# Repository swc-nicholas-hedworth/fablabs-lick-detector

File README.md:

# Fablabs Lick Detector

Inspired by the Allen Institute's: https://github.com/AllenNeuralDynamics/harp.device.lickety-split

## 1. Introduction

Capacitive lick detection offer advantages in the accuracy and speed of lick/touch detection. The challenge comes when using it with ephys devices such as the neuropixel which can pickup the input signal from the touch detector as noise. Our lick detector was inspired by the Allen Institutes lick detector which is shown to have low impact on ephys recordings.

The goals for this device were as follows:
- Reliable lick detection
- Low noise on ephys readings
- Simple to adjust and debug
- Easy to manufacture
- Easy to adapt into your own design

## 2. Setup
### Power Supply Requirements
- Min. Voltage = 3V
- Max. Voltage = 5.5V
- Max Current Consumption = 70mA (regardless of input voltage).

The output TTL depends on the input VCC voltage. For example:
- If VCC = 3.3V, output TTL amplitude = 3.3V
- If VCC = 5V, output TTL amplitude = 5V

### Ground Connection
Although not strictly necessary, it is encouraged for the mouse to have a reference to the board's ground potential. Basically the mouse needs to touch a conductor which is connected to the board's 

#### Metalic Floor
if the floor the mouse stands on is conductive, you may connect this floor to the ground potential.

#### Ephys
If the mouse has an implanted ephys device, it is posssible to connect the board's ground to that of the implant's ground.

### Spout Connection
Using crocodile clip

## 3. Calibration

This section outlines how to set the positions of the potentiometers RV1 and RV2 without any specialised equipment.

If any steps do not work, see the debugging guide.

### Step 0: Theory
RV1 is used to set the oscillators gain. clockwise increases the gain. The goal is to have the gain as low as possible to produce a low amplitude and clean signal to the spout so as to not intefere with ephys measurements. At maximum gain the signal will be distorted, introducing harmonics to the signal which is undesireable. At a certain "minimum" gain the oscillator will stop working. The goal is to have the oscillator just turn on, this gives us the lowest circuit noise.

RV2 is used to set the output gain. clockwise increases the gain. The goal is to have gain as low as possible to achieve extremely fast response to lick events. The output signal goes through a schmitt trigger, ensuring the gain sets the output at just the point the schmitt trigger activates ensures the quickest response times.

### Step 1: Initial conditions
- Turn RV1 all the way clockwise. (max oscillator gain)
- Turn RV2 all the way anticlockwise (min output gain)

This condition ensures that the oscillator is working (although distorted) and that the LED is on.

### Step 2: Detection
- Turn RV2 clockwise until the LED turns off.

You should see the LED turn on when you touch the "SPOUT" pin, and turn back off when you stop touching

### Step 3: Refine
**The following steps reduce the amplitude of the oscillator, thereby giving lower noise to ephys measurements.**

- Turn RV1 anticlockwise until the LED turns on.
- Turn RV2 clockwise until the LED turns back off.
- Test that touching the "SPOUT" pin still turns the LED on.

### Step 4: Repeat

- Repeat Step 3 until the LED seizes to turn off or if the LED starts behaving weirdly.
- When you reach the point that the LED starts behaving weirdly, revert RV1 and RV2 back to the previous state when the LED was still operating successfully.

## 4. Test Results

This section is intended to show the typical performance of the lick detector at each test point, showing how individual parts of the circuit should perform under normal conditions.

A Keysight DSOX1204A was used to capture the waveform and calculate the FFT. A custom BNC to pin header cable was created to feed signals from the board to the oscilloscope.

### [VCC] Input Voltage
The input voltage is used to power the dual supply converter on the board and the output stage op-amp (see amp and TTL test points).

### [V+] Positive Voltage Rail
This supply rail is generated by the dual supply converter.

### [V-] Negative Voltage Rail
This supply rail is generated by the dual supply converter.

### [osc] Oscillator

### [out] Signal to Spout

### [buf] Buffered Signal from Spout

### [hwr] Half Wave Rectifier

### [pfwr] Precision Full Wave Rectifier

### [lpf] Low-Pass Filter

### [amp] Amplifier 

### [TTL] Final Output TTL

### 5. EMI Performance

This section focuses on how the lick detectors near field noise looks like.

#### E-Field

#### H-Field

### 6. Impact on Ephys Recordings

This section evaluates the impact of noise on Ephys Recordings.

A mouse will lick from a spout. We will collect the following readings:
1. **Control**: 
2. **Grounded to Ephys**:
3. **Grounded to Ephys and Conductive Floor**:

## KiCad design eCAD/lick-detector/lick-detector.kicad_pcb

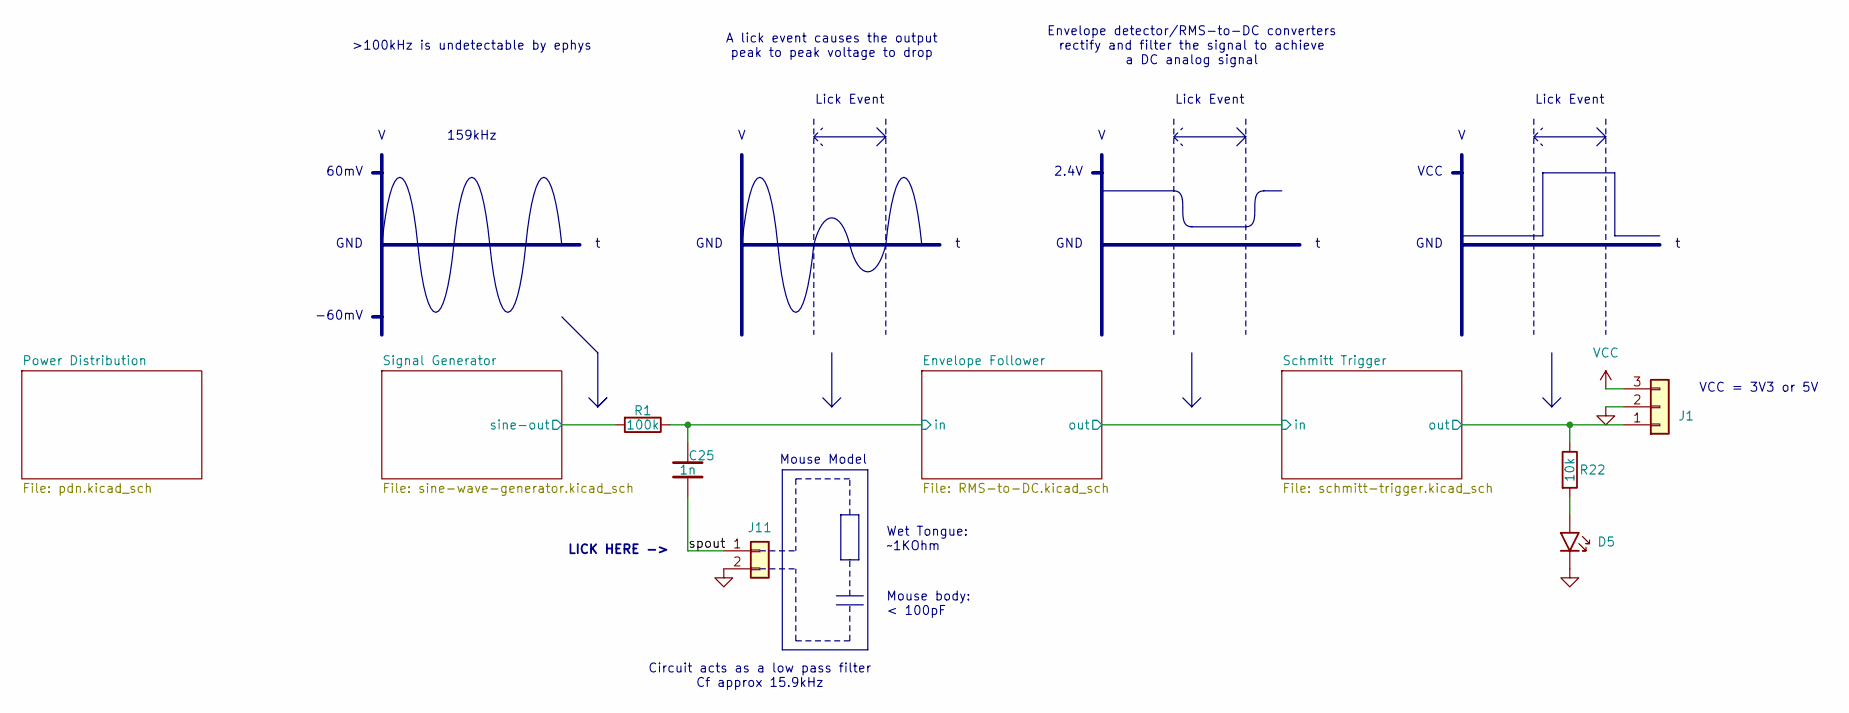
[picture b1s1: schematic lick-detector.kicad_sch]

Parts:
C25: 1n; C_0603_1608M; Part Version 0.0.0; JLCPCB Part # C1588
D5: !LED; LED_0805_2012M; Part Version 0.0.0; JLCPCB Part # C2297
J1: J_PinHeader_01x03_2.54_V; MFR.Part # PZ254V-11-03P; JLCPCB Part # C2937625
J11: J_PinHeader_01x02_2.54_V; MFR.Part # PZ254V-11-02P; JLCPCB Part # C492401
R1: 100k; R_0603_1608M; Part Version 0.0.0; JLCPCB Part # C25803
R22: 10k; R_0603_1608M; Part Version 0.0.0; JLCPCB Part # C25804

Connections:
/RMS-to-DC/in: C25.2, R1.2; also elsewhere on the board
/schmitt-trigger/out: J1.1, R22.2; also elsewhere on the board
/sine-wave-generator/out: R1.1; also elsewhere on the board
/spout: C25.1, J11.1
GND: D5.1 (K), J1.2, J11.2; also elsewhere on the board
unnamed: D5.2 (A), R22.1
VCC: J1.3; also elsewhere on the board

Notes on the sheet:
Lick Event
VCC
A lick event causes the output peak to peak voltage to drop
159kHz
GND
2.4V
>100kHz is undetectable by ephys
Wet Tongue: ~1KOhm
Mouse Model
-60mV
Envelope detector/RMS-to-DC converters rectify and filter the signal to achieve a DC analog signal
LICK HERE ->
VCC = 3V3 or 5V
Mouse body: < 100pF
Circuit acts as a low pass filter Cf approx 15.9kHz
60mV

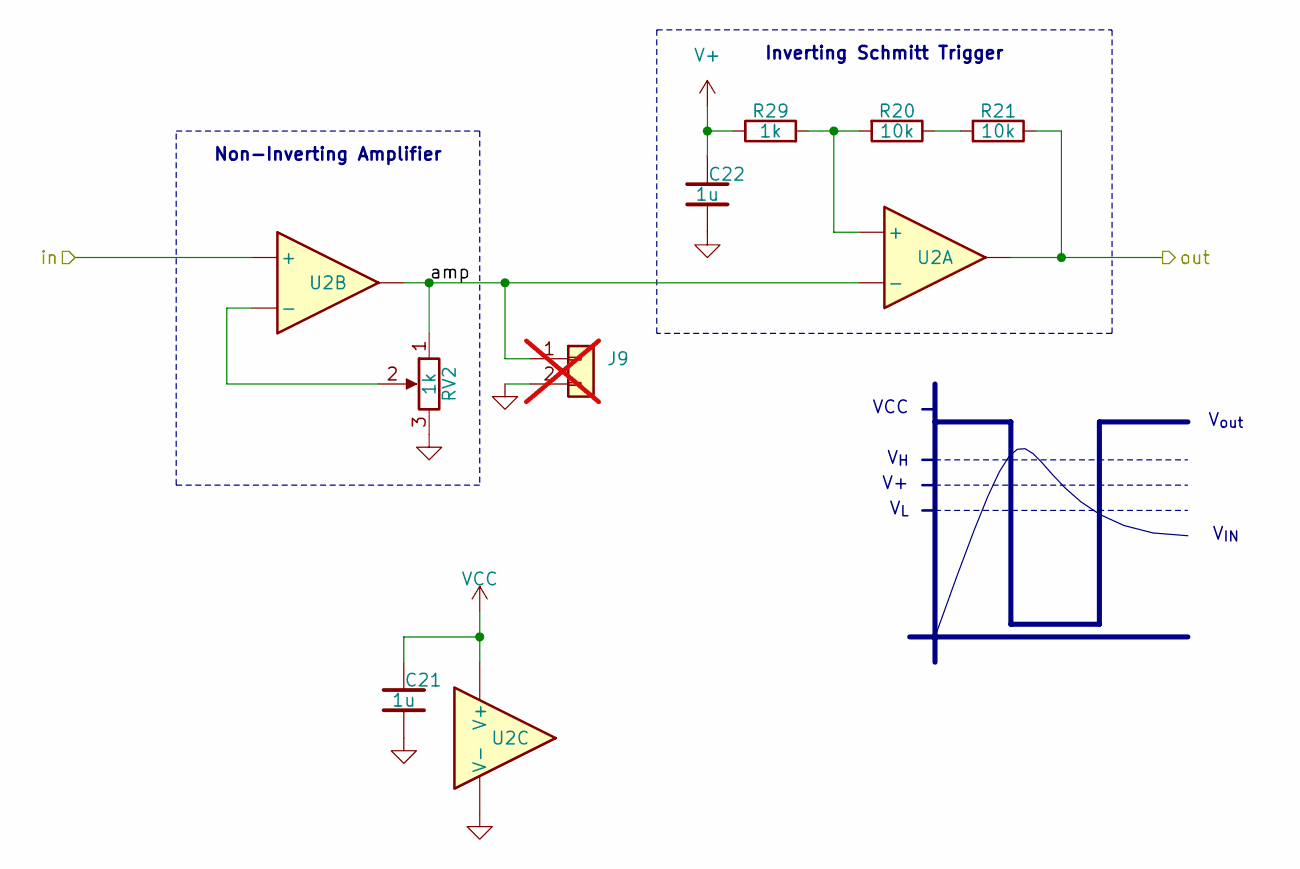
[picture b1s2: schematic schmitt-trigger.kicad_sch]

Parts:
C21, C22: 1u; C_0603_1608M; Part Version 0.0.0; JLCPCB Part # C15849
J9: J_PinHeader_01x02_2.54_V; MFR.Part # PZ254V-11-02P; JLCPCB Part # C492401; not fitted
R20, R21: 10k; R_0603_1608M; Part Version 0.0.0; JLCPCB Part # C25804
R29: 1k; R_0603_1608M; Part Version 0.0.0; JLCPCB Part # C22962
RV2: 1k; 3314J-1-102E; Part Version 0.0.0; JLCPCB Part # C124640
U2: OPA2365; SOIC-8_3.9x4.9mm; Part Version 0.0.0; JLCPCB Part # C130011

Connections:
/RMS-to-DC/lpf: U2.5 (+); also elsewhere on the board
/schmitt-trigger/amp: J9.1, RV2.1, U2.2 (-), U2.7
/schmitt-trigger/out: R21.2, U2.1; also elsewhere on the board
GND: C21.1, C22.1, J9.2, RV2.3, U2.4 (V-); also elsewhere on the board
unnamed: R20.2, R21.1
unnamed: R20.1, R29.1, U2.3 (+)
unnamed: RV2.2, U2.6 (-)
V+: C22.2, R29.2; also elsewhere on the board
VCC: C21.2, U2.8 (V+); also elsewhere on the board

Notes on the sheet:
V_{L}
V_{H}
VCC
V_{out}
V_{IN}
Inverting Schmitt Trigger
Non-Inverting Amplifier

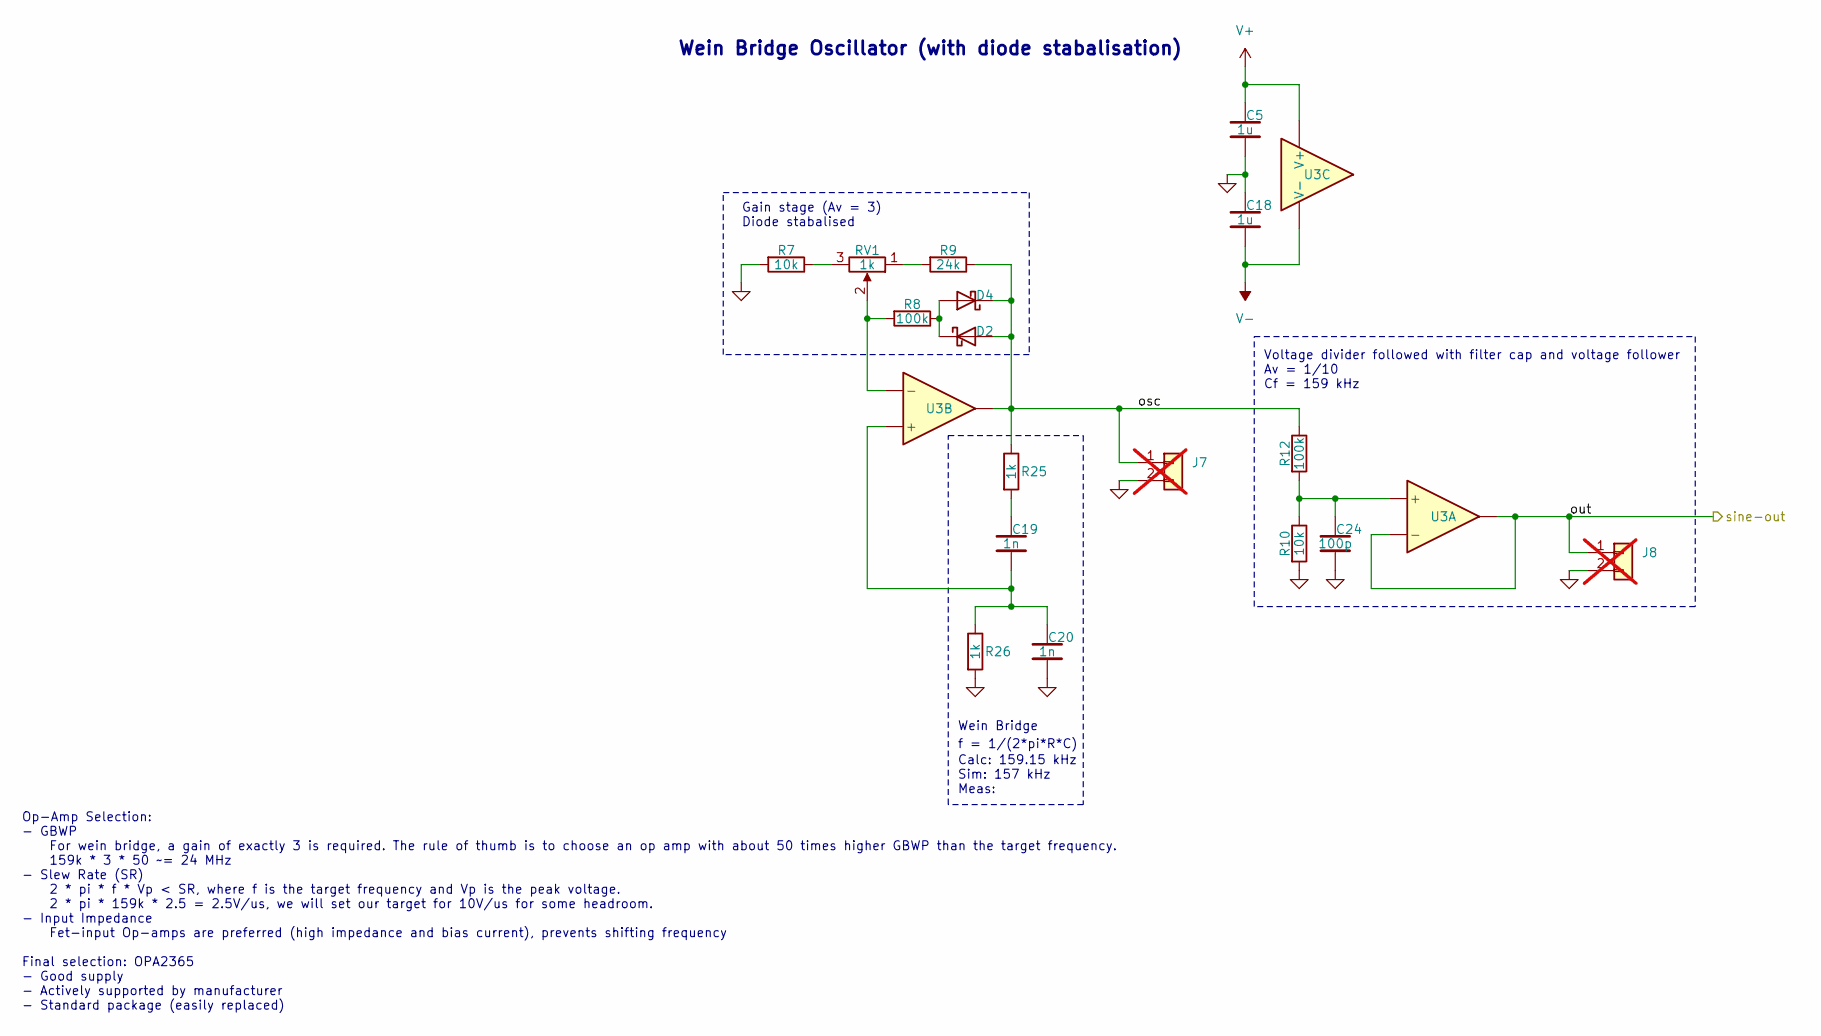
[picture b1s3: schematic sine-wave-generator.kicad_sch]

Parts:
C5, C18: 1u; C_0603_1608M; Part Version 0.0.0; JLCPCB Part # C15849
C19, C20: 1n; C_0603_1608M; Part Version 0.0.0; JLCPCB Part # C1588
C24: 100p; C_0603_1608M; Part Version 0.0.0; JLCPCB Part # C14858
D2, D4: BAT54; SOD-323; Part Version 0.0.0; JLCPCB Part # C21107
J7, J8: J_PinHeader_01x02_2.54_V; MFR.Part # PZ254V-11-02P; JLCPCB Part # C492401; not fitted
R7, R10: 10k; R_0603_1608M; Part Version 0.0.0; JLCPCB Part # C25804
R8, R12: 100k; R_0603_1608M; Part Version 0.0.0; JLCPCB Part # C25803
R9: 24k; R_0603_1608M; Part Version 0.0.0; JLCPCB Part # C23352
R25, R26: 1k; R_0603_1608M; Part Version 0.0.0; JLCPCB Part # C22962
RV1: 1k; 3314J-1-102E; Part Version 0.0.0; JLCPCB Part # C124640
U3: OPA2365; SOIC-8_3.9x4.9mm; Part Version 0.0.0; JLCPCB Part # C130011

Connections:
/sine-wave-generator/osc: D2.2 (A), D4.1 (K), J7.1, R9.2, R12.2, R25.2, U3.7
/sine-wave-generator/out: J8.1, U3.1, U3.2 (-); also elsewhere on the board
GND: C5.1, C18.2, C20.1, C24.1, J7.2, J8.2, R7.1, R10.1, R26.1; also elsewhere on the board
unnamed: C19.2, R25.1
unnamed: D2.1 (K), D4.2 (A), R8.2
unnamed: R7.2, RV1.3
unnamed: R9.1, RV1.1
unnamed: C24.2, R10.2, R12.1, U3.3 (+)
unnamed: C19.1, C20.2, R26.2, U3.5 (+)
unnamed: R8.1, RV1.2, U3.6 (-)
V+: C5.2, U3.8 (V+); also elsewhere on the board
V-: C18.1, U3.4 (V-); also elsewhere on the board

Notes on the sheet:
f = 1/(2*pi*R*C)
Gain stage (Av = 3) Diode stabalised
Calc: 159.15 kHz Sim: 157 kHz Meas:
Op-Amp Selection: - GBWP For wein bridge, a gain of exactly 3 is required. The rule of thumb is to choose an op amp with about 50 times higher GBWP than the target frequency. 159k * 3 * 50 ~= 24 MHz - Slew Rate (SR) 2 * pi * f * Vp < SR, where f is the target frequency and Vp is the peak voltage. 2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
Voltage divider followed with filter cap and voltage follower Av = 1/10 Cf = 159 kHz
Wein Bridge Oscillator (with diode stabalisation)
Wein Bridge

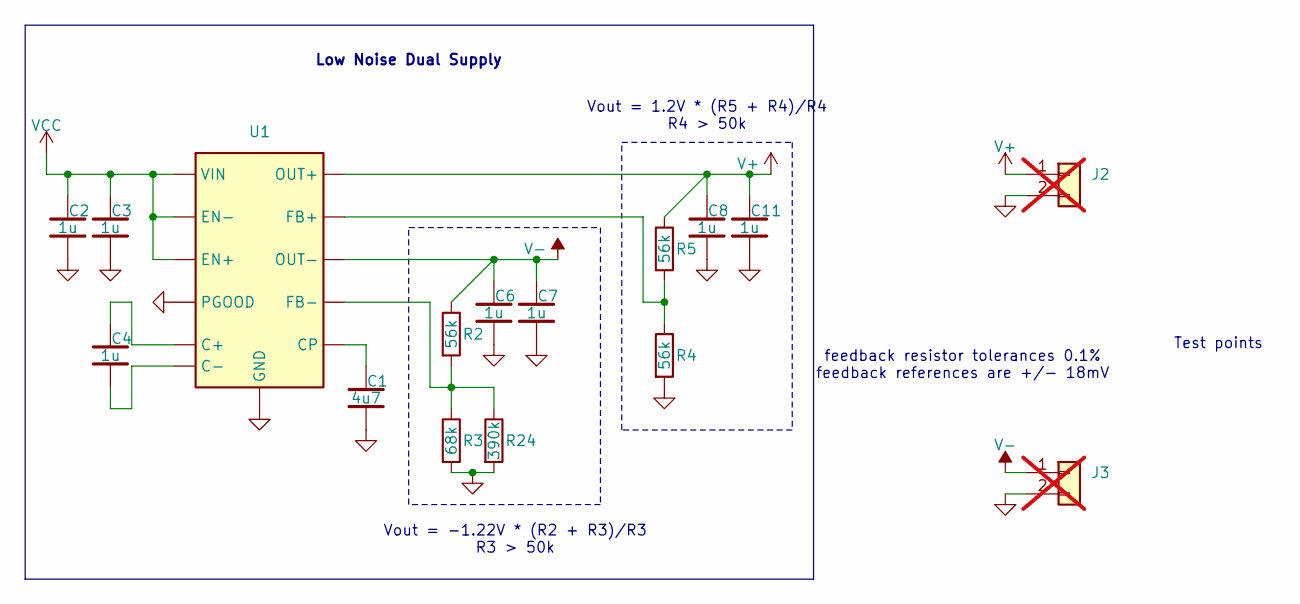
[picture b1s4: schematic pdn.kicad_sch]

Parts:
C1: 4u7; C_0603_1608M; Part Version 0.0.0; JLCPCB Part # C19666
C2, C3, C4, C6, C7, C8, C11: 1u; C_0603_1608M; Part Version 0.0.0; JLCPCB Part # C15849
J2, J3: J_PinHeader_01x02_2.54_V; MFR.Part # PZ254V-11-02P; JLCPCB Part # C492401; not fitted
R2, R4, R5: 56k; R_0603_1608M; Part Version 0.0.0; JLCPCB Part # C23206
R3: 68k; R_0603_1608M; Part Version 0.0.0; JLCPCB Part # C23231
R24: 390k; R_0603_1608M; Part Version 0.0.0; JLCPCB Part # C137735
U1: LM27762DSSR; WSON-12-EP; MFR.Part # LM27762DSSR; JLCPCB Part # C473398

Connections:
GND: C1.1, C2.1, C3.1, C6.1, C7.1, C8.1, C11.1, J2.2, J3.2, R3.1, R4.1, R24.1, U1.1 (PGOOD), U1.4 (GND), U1.13 (PAD); also elsewhere on the board
unnamed: C4.2, U1.10 (C+)
unnamed: C4.1, U1.9 (C-)
unnamed: C1.2, U1.5 (CP)
unnamed: R4.2, R5.1, U1.2 (FB+)
unnamed: R2.1, R3.2, R24.2, U1.7 (FB-)
V+: C8.2, C11.2, J2.1, R5.2, U1.11 (OUT+); also elsewhere on the board
V-: C6.2, C7.2, J3.1, R2.2, U1.6 (OUT-); also elsewhere on the board
VCC: C2.2, C3.2, U1.3 (VIN), U1.8 (EN-), U1.12 (EN+); also elsewhere on the board

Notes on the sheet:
Test points
feedback resistor tolerances 0.1% feedback references are +/- 18mV
Vout = 1.2V * (R5 + R4)/R4 R4 > 50k
Low Noise Dual Supply
Vout = -1.22V * (R2 + R3)/R3 R3 > 50k

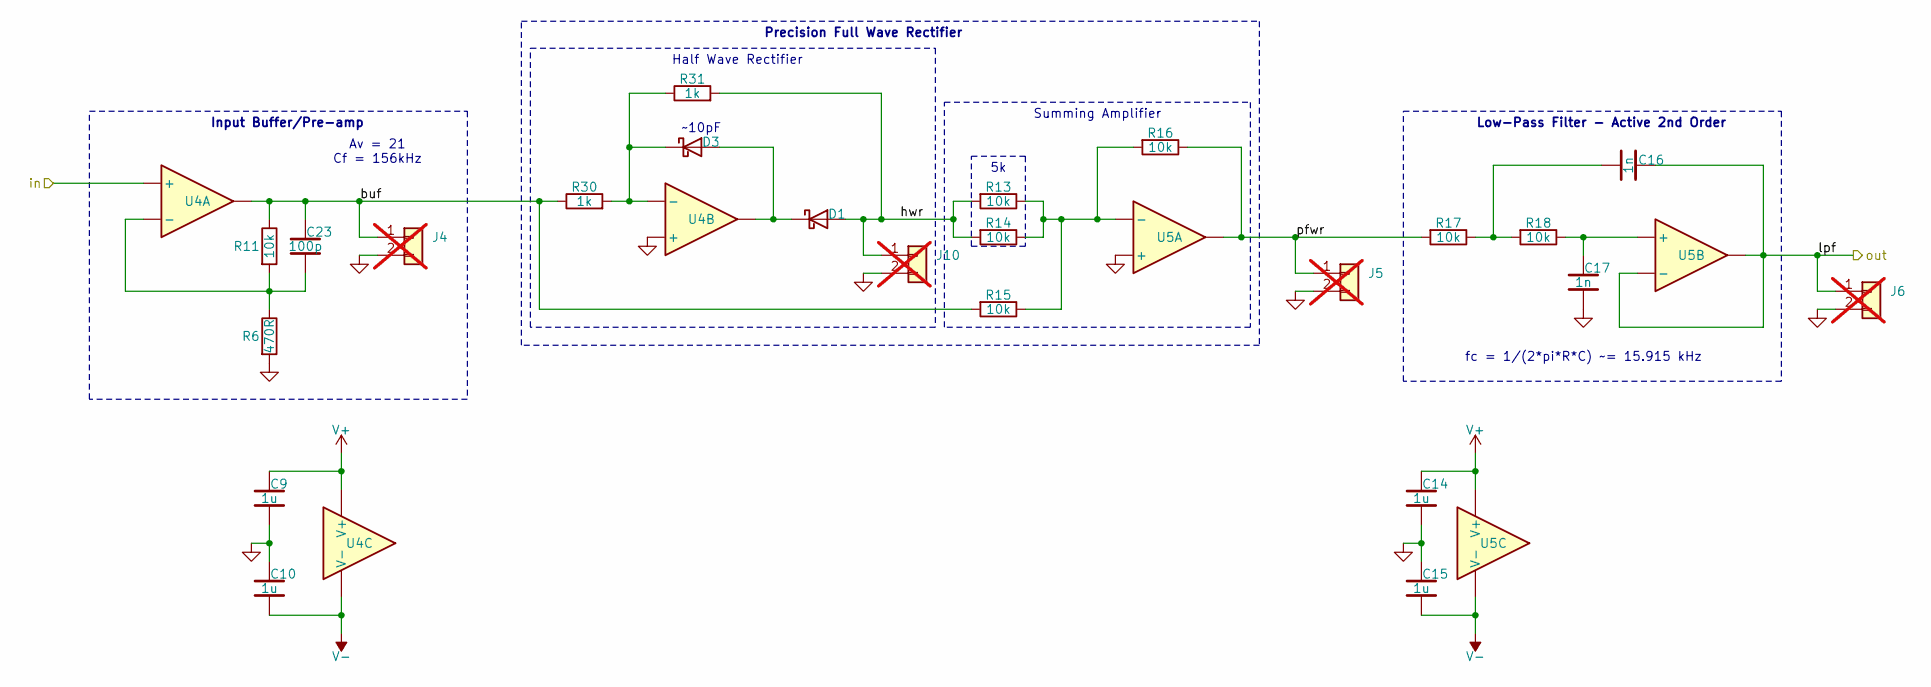
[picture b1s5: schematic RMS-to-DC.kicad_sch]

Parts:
C9, C10, C14, C15: 1u; C_0603_1608M; Part Version 0.0.0; JLCPCB Part # C15849
C16, C17: 1n; C_0603_1608M; Part Version 0.0.0; JLCPCB Part # C1588
C23: 100p; C_0603_1608M; Part Version 0.0.0; JLCPCB Part # C14858
D1, D3: BAT54; SOD-323; Part Version 0.0.0; JLCPCB Part # C21107
J4, J5, J6, J10: J_PinHeader_01x02_2.54_V; MFR.Part # PZ254V-11-02P; JLCPCB Part # C492401; not fitted
R6: 470R; R_0603_1608M; Part Version 0.0.0; JLCPCB Part # C23179
R11, R13, R14, R15, R16, R17, R18: 10k; R_0603_1608M; Part Version 0.0.0; JLCPCB Part # C25804
R30, R31: 1k; R_0603_1608M; Part Version 0.0.0; JLCPCB Part # C22962
U4, U5: OPA2365; SOIC-8_3.9x4.9mm; Part Version 0.0.0; JLCPCB Part # C130011

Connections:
/RMS-to-DC/buf: C23.2, J4.1, R11.2, R15.1, R30.2, U4.1
/RMS-to-DC/hwr: D1.2 (A), J10.1, R13.1, R14.1, R31.1
/RMS-to-DC/in: U4.3 (+); also elsewhere on the board
/RMS-to-DC/lpf: C16.2, J6.1, U5.6 (-), U5.7; also elsewhere on the board
/RMS-to-DC/pfwr: J5.1, R16.2, R17.1, U5.1
GND: C9.1, C10.2, C14.1, C15.2, C17.1, J4.2, J5.2, J6.2, J10.2, R6.1, U4.5 (+), U5.3 (+); also elsewhere on the board
unnamed: C16.1, R17.2, R18.1
unnamed: D1.1 (K), D3.2 (A), U4.7
unnamed: D3.1 (K), R30.1, R31.2, U4.6 (-)
unnamed: C23.1, R6.2, R11.1, U4.2 (-)
unnamed: R13.2, R14.2, R15.2, R16.1, U5.2 (-)
unnamed: C17.2, R18.2, U5.5 (+)
V+: C9.2, C14.2, U4.8 (V+), U5.8 (V+); also elsewhere on the board
V-: C10.1, C15.1, U4.4 (V-), U5.4 (V-); also elsewhere on the board

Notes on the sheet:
fc = 1/(2*pi*R*C) ~= 15.915 kHz
Low-Pass Filter - Active 2nd Order
Input Buffer/Pre-amp
Half Wave Rectifier
Summing Amplifier
~10pF
Precision Full Wave Rectifier
Av = 21 Cf = 156kHz

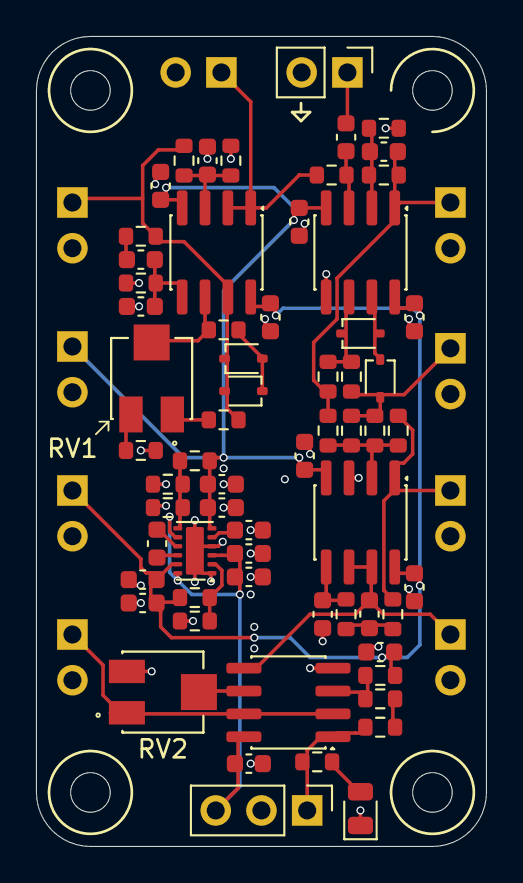
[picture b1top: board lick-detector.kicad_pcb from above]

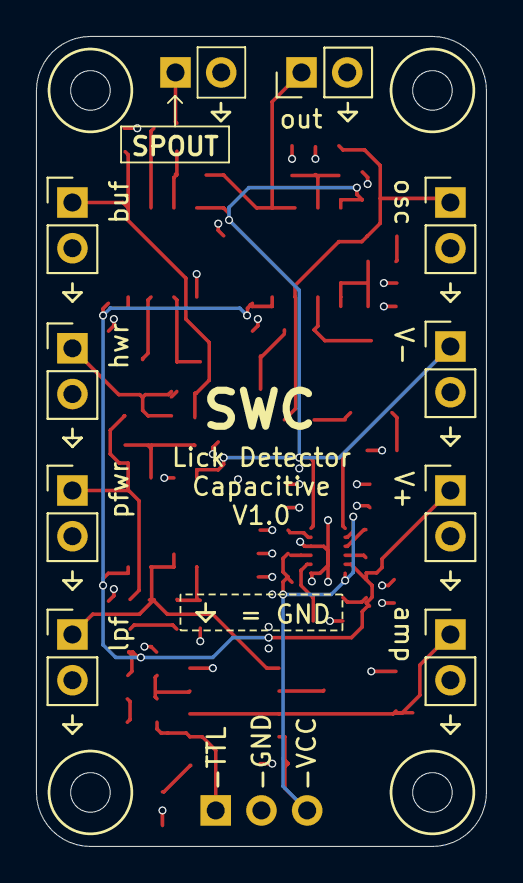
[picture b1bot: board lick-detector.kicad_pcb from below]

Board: 4 copper layers, 25.0 x 45.0 mm, 73 parts (9 on the bottom side), 36 nets.

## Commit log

2026-06-16 Number of upgrades complete: - Lower amplitude sine wave generator - Improved debug connector layout - Brightness of LED decreased - README updated with guide and areas for documentation - .gitignore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
